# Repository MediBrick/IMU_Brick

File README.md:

# IMU / Activity Brick

This repository contains two generations of the MediBrick IMU board design.

## [v1 — IMU MediBrick](v1/README.md)

The original board, built around the TDK ICM-20948 9-axis IMU and Bosch
BMP581 pressure sensor with an SPI interface. This design is complete and has
been manufactured. ICM-20948 is no longer manufactured.

## [v2 — Activity Brick V2](v2/README.md)

A redesign around the Bosch BMI323 IMU, BMM350 magnetometer, BMP581
barometer, and an optional MAX-M10S or ZED-F9P GNSS/RTK receiver, interfacing
to an Adafruit Feather ESP32-S3 host.

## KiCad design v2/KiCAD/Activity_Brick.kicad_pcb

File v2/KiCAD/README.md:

# Activity Brick V2 KiCad libraries

This directory is ready to hold the Activity Brick V2 KiCad project. KiCad
automatically reads the three project library tables when the project is saved
in this directory.

- `ActivityBrickV2.kicad_pro`: KiCad 10 project entry point
- `ActivityBrickV2.kicad_sch`: main schematic
- `ActivityBrickV2.kicad_pcb`: PCB layout
- `symbols/ActivityBrick.kicad_symdir/`: unpacked project-local symbol library;
  store each symbol in its own `.kicad_sym` file
- `footprints/ActivityBrick.pretty/`: project-local footprint library; store each
  footprint in its own `.kicad_mod` file
- `3dmodels/ActivityBrick.3dshapes/`: project-local STEP and WRL models
- `design_blocks/ActivityBrick.kicad_blocks/`: reusable schematic and PCB blocks

The design-block library contains empty, valid schematic blocks for `Power`,
`Sensors`, `GNSS_MAX_M10S`, `GNSS_ZED_F9P`, and `Feather_Interface`.

The PCB intentionally has no board outline yet. DRC will report
`invalid_outline` until the mechanical board dimensions are defined on
`Edge.Cuts`.

## Creating a design block

1. Open the Activity Brick V2 project in KiCad 10.
2. In the Schematic or PCB Editor, select **View -> Panels -> Design Blocks**.
3. Select the `ActivityBrick` library.
4. Use **Save Selection as Design Block** or **Save Current Sheet as Design Block**.

Keep downloaded or generated symbols and footprints in these project-local
libraries so the design does not depend on a machine-specific global library.
Reference project-local models from footprints using paths such as
`${KIPRJMOD}/3dmodels/ActivityBrick.3dshapes/BMI323.step`.

## Manufacturer component pages

- [Bosch Sensortec BMI323](https://www.bosch-sensortec.com/en/products/motion-sensors/imus/bmi323)
- [Bosch Sensortec BMM350](https://www.bosch-sensortec.com/en/products/motion-sensors/magnetometers/bmm350)
- [Bosch Sensortec BMP581](https://www.bosch-sensortec.com/en/products/environmental-sensors/pressure-sensors/bmp581)
- [u-blox MAX-M10 series (MAX-M10S-00B)](https://www.u-blox.com/en/product/max-m10-series?legacy=Current)
- [u-blox ZED-F9P series (ZED-F9P-05B)](https://www.u-blox.com/en/product/zed-f9p-module)

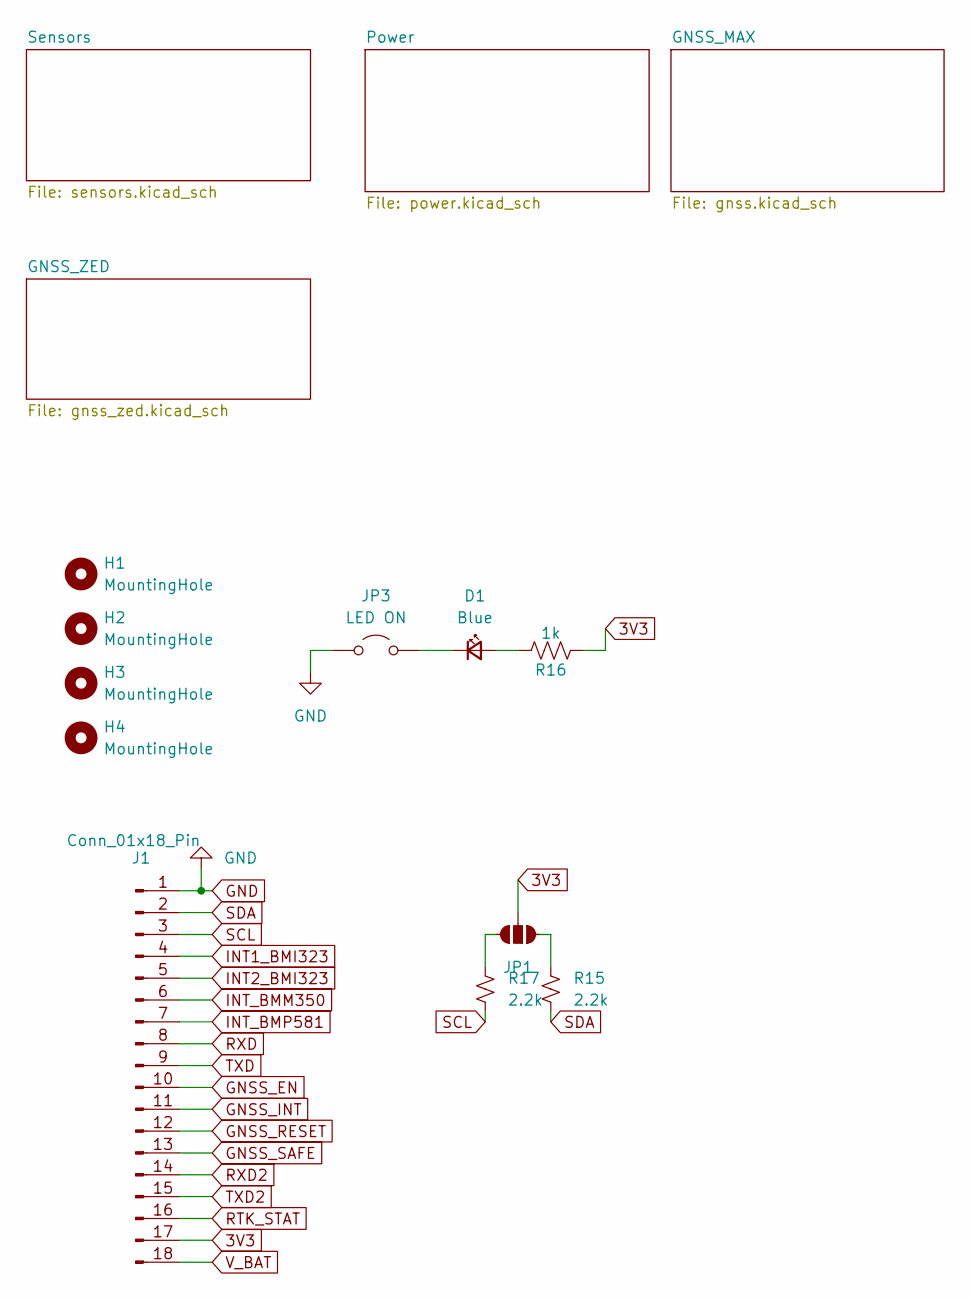
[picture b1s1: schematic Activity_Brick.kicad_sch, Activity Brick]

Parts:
D1: Blue; LED_0402_1005Metric_Red
H1, H2, H3, H4: MountingHole; MountingHole_3.5mm
J1: Conn_01x18_Pin; PinHeader_1x18_P2.54mm_Vertical
JP1: Jumper_3_NO
JP3: LED ON; Jumper_2_NO_NoSilk
R15, R17: 2.2k; R_0402_1005Metric
R16: 1k; R_0402_1005Metric

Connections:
3V3: J1.17, JP1.2 (B), R16.2; also elsewhere on the board
GND: J1.1, JP3.1 (A); also elsewhere on the board
GNSS_EN: J1.10; also elsewhere on the board
GNSS_INT: J1.11; also elsewhere on the board
GNSS_RESET: J1.12; also elsewhere on the board
GNSS_SAFE: J1.13; also elsewhere on the board
INT1_BMI323: J1.4; also elsewhere on the board
INT2_BMI323: J1.5; also elsewhere on the board
INT_BMM350: J1.6; also elsewhere on the board
INT_BMP581: J1.7; also elsewhere on the board
unnamed: D1.2 (A), R16.1
unnamed: D1.1 (K), JP3.2 (B)
unnamed: JP1.1 (A), R15.1
unnamed: JP1.3 (C), R17.1
RTK_STAT: J1.16; also elsewhere on the board
RXD: J1.8; also elsewhere on the board
RXD2: J1.14; also elsewhere on the board
SCL: J1.3, R17.2; also elsewhere on the board
SDA: J1.2, R15.2; also elsewhere on the board
TXD: J1.9; also elsewhere on the board
TXD2: J1.15; also elsewhere on the board
V_BAT: J1.18; also elsewhere on the board

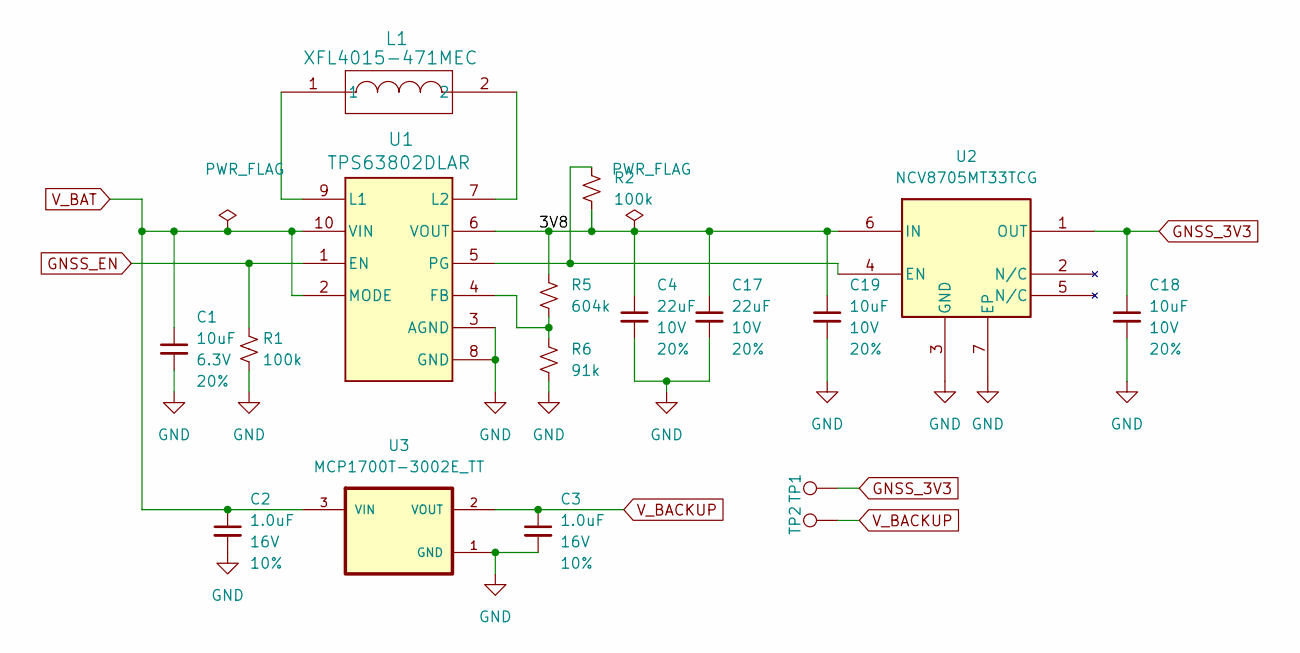
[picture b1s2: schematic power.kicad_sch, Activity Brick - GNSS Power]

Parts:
C1: 10uF; C_0603_1608Metric; Voltage 6.3V; Tolerance 20%
C2, C3: 1.0uF; C_0402_1005Metric; Voltage 16V; Tolerance 10%
C4, C17: 22uF; C_0603_1608Metric; Voltage 10V; Tolerance 20%
C18, C19: 10uF; C_0603_1608Metric; Voltage 10V; Tolerance 20%
L1: XFL4015-471MEC; IND_XFL4015_COC
R1, R2: 100k; R_0402_1005Metric
R5: 604k; R_0402_1005Metric
R6: 91k; R_0402_1005Metric
TP1, TP2: 1.0mm; TestPoint-1.0mm
U1: TPS63802DLAR; DLA0010A
U2: NCV8705MT33TCG; WDFN6_2X2_ONS_NCV8705
U3: MCP1700T-3002E_TT; SOT95P237X112-3N_MCP1700

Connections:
/Power/3V8: C4.1, C17.1, C19.1, R2.2, R5.2, U1.6 (VOUT), U2.6 (IN)
GND: C1.2, C2.2, C3.2, C4.2, C17.2, C18.2, C19.2, R1.2, R6.1, U1.3 (AGND), U1.8 (GND), U2.3 (GND), U2.7 (EP), U3.1 (GND); also elsewhere on the board
GNSS_3V3: C18.1, TP1.1 (1_1), U2.1 (OUT); also elsewhere on the board
GNSS_EN: R1.1, U1.1 (EN); also elsewhere on the board
unnamed: R5.1, R6.2, U1.4 (FB)
unnamed: L1.1, U1.9 (L1)
unnamed: L1.2, U1.7 (L2)
unnamed: R2.1, U1.5 (PG), U2.4 (EN)
V_BACKUP: C3.1, TP2.1 (1_1), U3.2 (VOUT); also elsewhere on the board
V_BAT: C1.1, C2.1, U1.2 (MODE), U1.10 (VIN), U3.3 (VIN); also elsewhere on the board

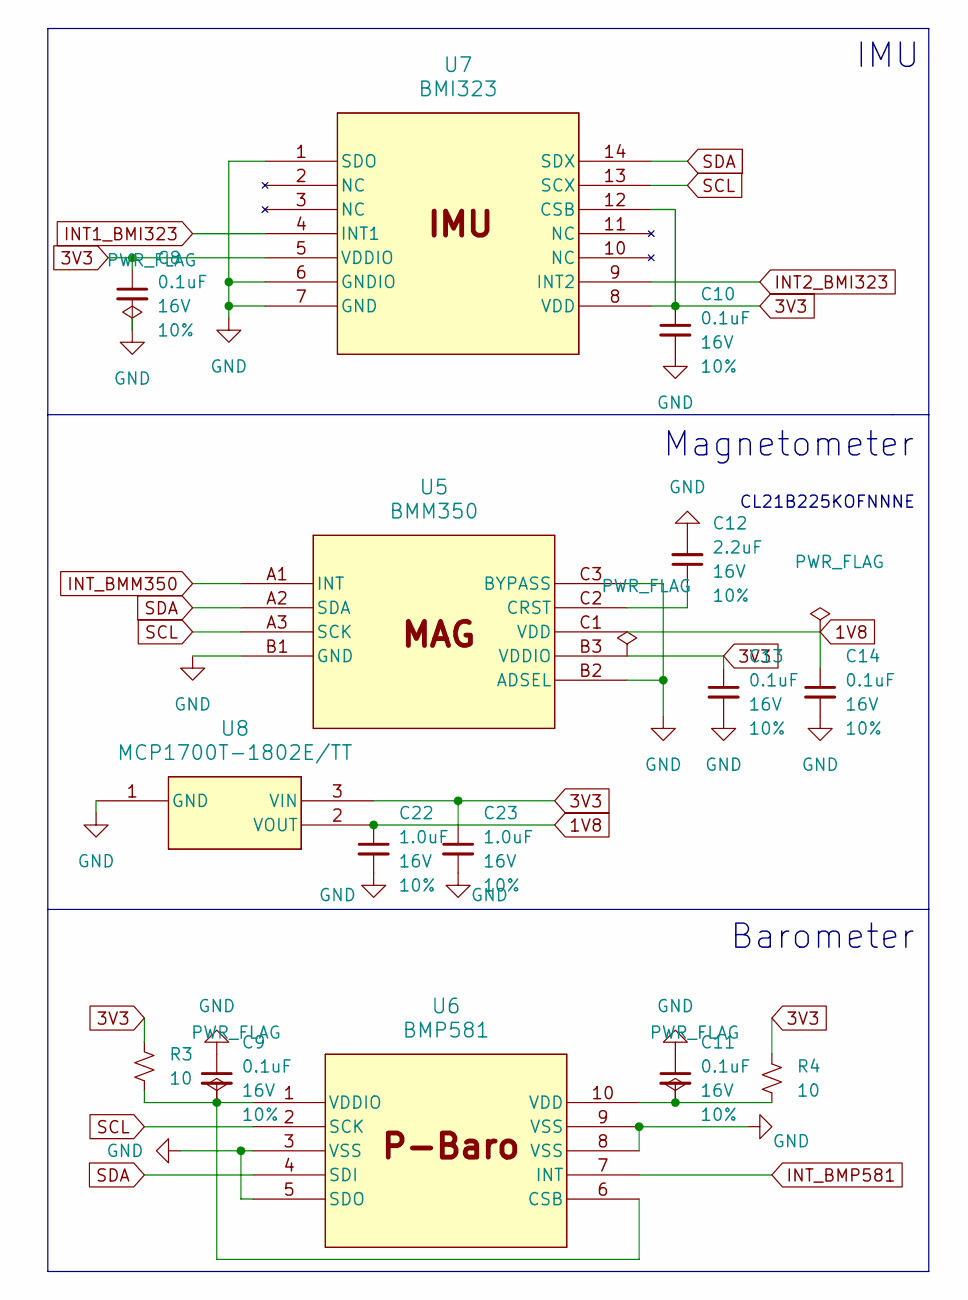
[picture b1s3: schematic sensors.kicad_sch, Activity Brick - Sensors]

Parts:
C8, C9, C10, C11, C13, C14: 0.1uF; C_0402_1005Metric; Voltage 16V; Tolerance 10%
C12: 2.2uF; C_0805_2012Metric; Voltage 16V; Tolerance 10%; MPN CL21B225KOFNNNE
C22, C23: 1.0uF; C_0402_1005Metric; Voltage 16V; Tolerance 10%
R3, R4: 10; R_0402_1005Metric
U5: BMM350; BGA9_BMM350_BOS
U6: BMP581; QFN10_BMP581_BOS
U7: BMI323; BMI323_BOS
U8: MCP1700T-1802E/TT; SOT95P237X112-3N_MCP1700_1802

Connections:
1V8: C14.1, C22.1, U5.C1 (VDD), U8.2 (VOUT)
3V3: C8.1, C10.1, C13.1, C23.1, R3.2, R4.2, U5.B3 (VDDIO), U7.5 (VDDIO), U7.8 (VDD), U7.12 (CSB), U8.3 (VIN); also elsewhere on the board
GND: C8.2, C9.1, C10.2, C11.1, C12.2, C13.2, C14.2, C22.2, C23.2, U5.B1 (GND), U5.B2 (ADSEL), U5.C3 (BYPASS), U6.3 (VSS), U6.5 (SDO), U6.8 (VSS), U6.9 (VSS), U7.1 (SDO), U7.6 (GNDIO), U7.7 (GND), U8.1 (GND); also elsewhere on the board
INT1_BMI323: U7.4 (INT1); also elsewhere on the board
INT2_BMI323: U7.9 (INT2); also elsewhere on the board
INT_BMM350: U5.A1 (INT); also elsewhere on the board
INT_BMP581: U6.7 (INT); also elsewhere on the board
unnamed: C12.1, U5.C2 (CRST)
unnamed: C9.2, R3.1, U6.1 (VDDIO), U6.6 (CSB)
unnamed: C11.2, R4.1, U6.10 (VDD)
SCL: U5.A3 (SCK), U6.2 (SCK), U7.13 (SCX); also elsewhere on the board
SDA: U5.A2 (SDA), U6.4 (SDI), U7.14 (SDX); also elsewhere on the board

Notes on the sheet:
Magnetometer
CL21B225KOFNNNE
IMU
Barometer

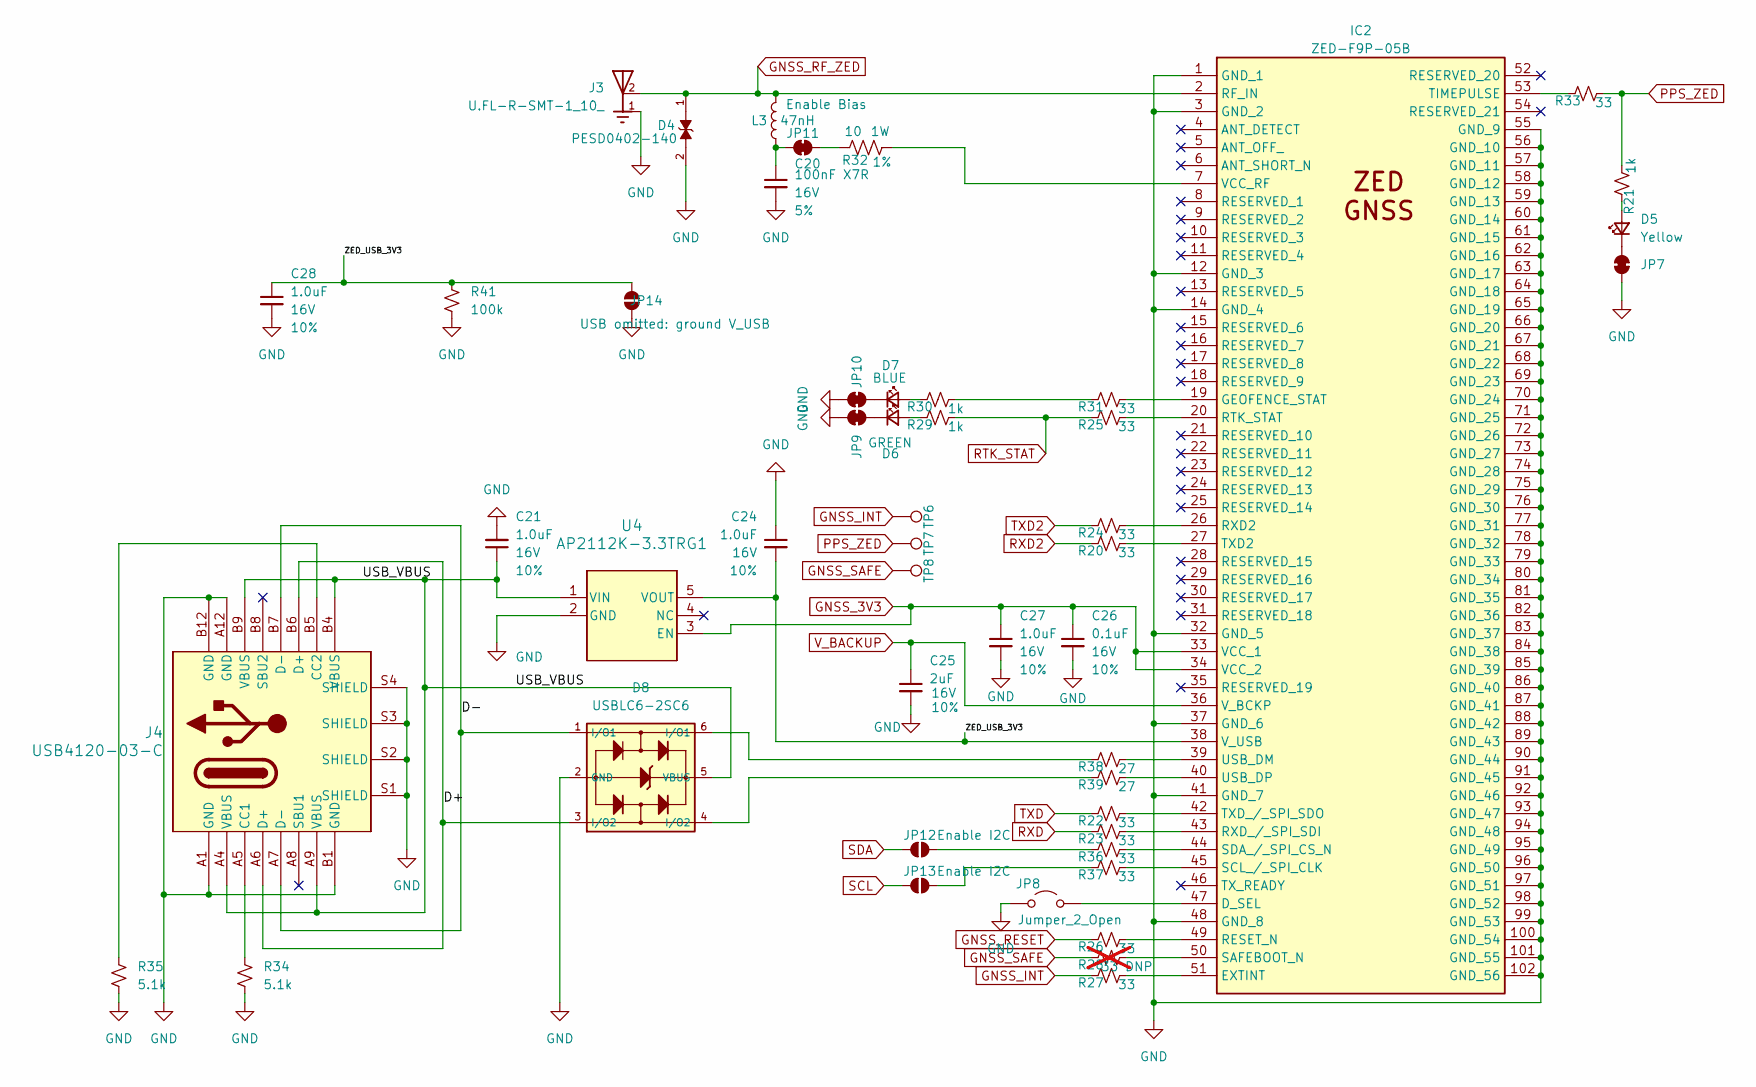
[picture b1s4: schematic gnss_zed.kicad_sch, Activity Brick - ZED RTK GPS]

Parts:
C20: 100nF X7R; C_0402_1005Metric; Voltage 16V; Tolerance 5%; Part Murata GRM155R71C104JA88D
C21, C24, C27, C28: 1.0uF; C_0402_1005Metric; Voltage 16V; Tolerance 10%
C25: 2uF; C_0402_1005Metric; Voltage 16V; Tolerance 10%
C26: 0.1uF; C_0402_1005Metric; Voltage 16V; Tolerance 10%
D4: PESD0402-140; DIO_PESD0402-140; PARTREV 2016
D5: Yellow; LED_0402_1005Metric_Red
D6: GREEN; LED_0402_1005Metric_Red
D7: BLUE; LED_0402_1005Metric_Red
D8: USBLC6-2SC6; USBLC6-2SC6_SOT23-6L
IC2: ZED-F9P-05B; ZEDF9P05B; Manufacturer_Part_Number ZED-F9P-05B; Mouser Part Number 134-ZED-F9P-05B
J3: U.FL-R-SMT-1_10_; HRS_U.FL-R-SMT-1_10_
J4: USB4120-03-C; USB4120-03-C_GCT
JP7, JP9, JP10: Jumper_2_NC_Trace
JP8: Jumper_2_Open; Jumper_2_NO
JP11: Enable Bias; Jumper_2_NC_Trace
JP12, JP13: Enable I2C; Jumper_2_NO
JP14: USB omitted: ground V_USB; Jumper_2_NO
L3: 47nH; L_0402_1005Metric; Part Murata LQG15HS47NJ02D
R20, R22, R23, R24, R25, R26, R27, R31, R33, R36, R37: 33; R_0402_1005Metric
R21, R29, R30: 1k; R_0402_1005Metric
R28: 33 DNP; R_0402_1005Metric; not fitted
R32: 10; R_2010_5025Metric; Tolerance 1%; Part Bourns CMP2010-FX-10R0ELF
R34, R35: 5.1k; R_0402_1005Metric
R38, R39: 27; R_0402_1005Metric
R41: 100k; R_0402_1005Metric
TP6, TP7, TP8: 1.0mm; TestPoint-1.0mm
U4: AP2112K-3.3TRG1; SOT_RG1_DIO_AP2112K

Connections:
/GNSS_ZED/D+: D8.3 (I/O2), J4.A6 (D+), J4.B6 (D+)
/GNSS_ZED/D-: D8.1 (I/O1), J4.A7 (D-), J4.B7 (D-)
/GNSS_ZED/USB_VBUS: C21.1, D8.5 (VBUS), J4.A4 (VBUS), J4.A9 (VBUS), J4.B4 (VBUS), J4.B9 (VBUS), U4.1 (VIN)
/GNSS_ZED/ZED_USB_3V3: C24.2, C28.1, IC2.38 (V_USB), JP14.2 (B), R41.2, U4.5 (VOUT)
GND: C20.2, C21.2, C24.1, C25.2, C26.2, C27.2, C28.2, D4.2, D8.2 (GND), IC2.1 (GND_1), IC2.3 (GND_2), IC2.12 (GND_3), IC2.14 (GND_4), IC2.32 (GND_5), IC2.37 (GND_6), IC2.41 (GND_7), IC2.48 (GND_8), IC2.55 (GND_9), IC2.56 (GND_10), IC2.57 (GND_11), IC2.58 (GND_12), IC2.59 (GND_13), IC2.60 (GND_14), IC2.61 (GND_15), IC2.62 (GND_16), IC2.63 (GND_17), IC2.64 (GND_18), IC2.65 (GND_19), IC2.66 (GND_20), IC2.67 (GND_21), IC2.68 (GND_22), IC2.69 (GND_23), IC2.70 (GND_24), IC2.71 (GND_25), IC2.72 (GND_26), IC2.73 (GND_27), IC2.74 (GND_28), IC2.75 (GND_29), IC2.76 (GND_30), IC2.77 (GND_31), IC2.78 (GND_32), IC2.79 (GND_33), IC2.80 (GND_34), IC2.81 (GND_35), IC2.82 (GND_36), IC2.83 (GND_37), IC2.84 (GND_38), IC2.85 (GND_39), IC2.86 (GND_40), IC2.87 (GND_41), IC2.88 (GND_42), IC2.89 (GND_43), IC2.90 (GND_44), IC2.91 (GND_45), IC2.92 (GND_46), IC2.93 (GND_47), IC2.94 (GND_48), IC2.95 (GND_49), IC2.96 (GND_50), IC2.97 (GND_51), IC2.98 (GND_52), IC2.99 (GND_53), IC2.100 (GND_54), IC2.101 (GND_55), IC2.102 (GND_56), J3.1, J3.3, J4.A1 (GND), J4.A12 (GND), J4.B1 (GND), J4.B12 (GND), J4.S1 (SHIELD), J4.S2 (SHIELD), J4.S3 (SHIELD), J4.S4 (SHIELD), JP7.1 (A), JP8.1 (A), JP9.1 (A), JP10.1 (A), JP14.1 (A), R34.1, R35.1, R41.1, U4.2 (GND); also elsewhere on the board
GNSS_3V3: C26.1, C27.1, IC2.33 (VCC_1), IC2.34 (VCC_2), U4.3 (EN); also elsewhere on the board
GNSS_INT: R27.1, TP6.1 (1_1); also elsewhere on the board
GNSS_RESET: R26.1; also elsewhere on the board
GNSS_RF_ZED: D4.1, IC2.2 (RF_IN), J3.2, L3.2
GNSS_SAFE: R28.1, TP8.1 (1_1); also elsewhere on the board
unnamed: D5.2 (A), R21.1
unnamed: D5.1 (K), JP7.2 (B)
unnamed: D6.2 (A), R29.1
unnamed: D6.1 (K), JP9.2 (B)
unnamed: D7.2 (A), R30.1
unnamed: D7.1 (K), JP10.2 (B)
unnamed: D8.6 (I/O1), R38.1
unnamed: D8.4 (I/O2), R39.1
unnamed: IC2.47 (D_SEL), JP8.2 (B)
unnamed: IC2.51 (EXTINT), R27.2
unnamed: IC2.19 (GEOFENCE_STAT), R31.2
unnamed: IC2.49 (RESET_N), R26.2
unnamed: IC2.20 (RTK_STAT), R25.2
unnamed: IC2.26 (RXD2), R24.2
unnamed: IC2.43 (RXD_/_SPI_SDI), R23.2
unnamed: IC2.50 (SAFEBOOT_N), R28.2
unnamed: IC2.45 (SCL_/_SPI_CLK), R37.2
unnamed: IC2.44 (SDA_/_SPI_CS_N), R36.2
unnamed: IC2.53 (TIMEPULSE), R33.1
unnamed: IC2.27 (TXD2), R20.2
unnamed: IC2.42 (TXD_/_SPI_SDO), R22.2
unnamed: IC2.39 (USB_DM), R38.2
unnamed: IC2.40 (USB_DP), R39.2
unnamed: IC2.7 (VCC_RF), R32.2
unnamed: J4.A5 (CC1), R34.2
unnamed: J4.B5 (CC2), R35.2
unnamed: C20.1, JP11.1 (A), L3.1
unnamed: JP11.2 (B), R32.1
unnamed: JP12.2 (B), R36.1
unnamed: JP13.2 (B), R37.1
unnamed: R30.2, R31.1
PPS_ZED: R21.2, R33.2, TP7.1 (1_1)
RTK_STAT: R25.1, R29.2; also elsewhere on the board
RXD: R23.1; also elsewhere on the board
RXD2: R20.1; also elsewhere on the board
SCL: JP13.1 (A); also elsewhere on the board
SDA: JP12.1 (A); also elsewhere on the board
TXD: R22.1; also elsewhere on the board
TXD2: R24.1; also elsewhere on the board
V_BACKUP: C25.1, IC2.36 (V_BCKP); also elsewhere on the board

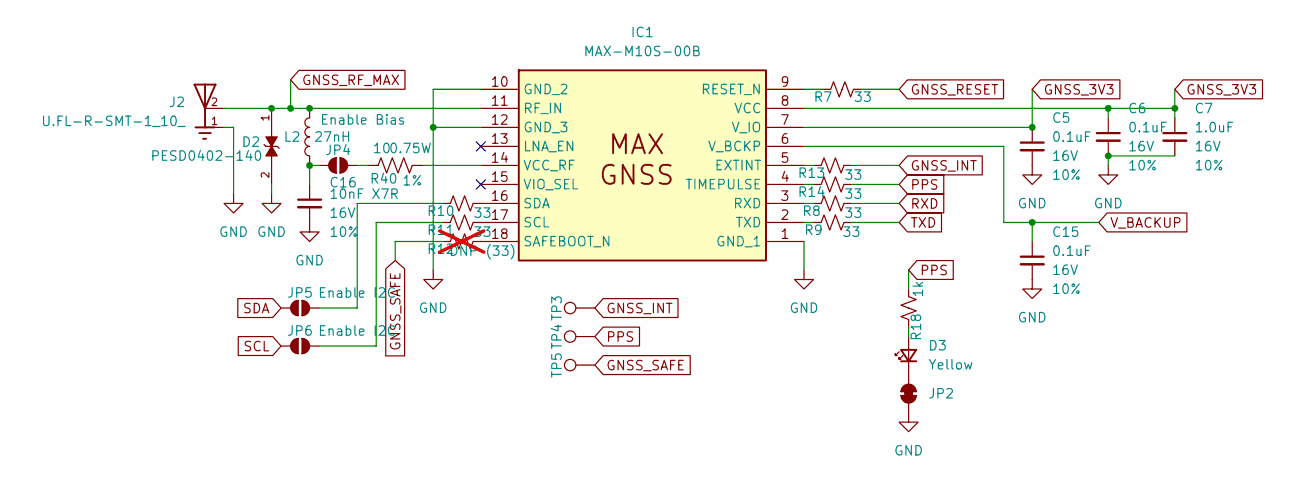
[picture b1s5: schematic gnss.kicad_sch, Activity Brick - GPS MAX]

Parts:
C5, C6, C15: 0.1uF; C_0402_1005Metric; Voltage 16V; Tolerance 10%
C7: 1.0uF; C_0402_1005Metric; Voltage 16V; Tolerance 10%
C16: 10nF X7R; C_0402_1005Metric; Voltage 16V; Tolerance 10%
D2: PESD0402-140; DIO_PESD0402-140; PARTREV 2016
D3: Yellow; LED_0402_1005Metric_Red
IC1: MAX-M10S-00B; MAXM10S00B; Manufacturer_Part_Number MAX-M10S-00B; Mouser Part Number 377-MAX-M10S-00B
J2: U.FL-R-SMT-1_10_; HRS_U.FL-R-SMT-1_10_
JP2: Jumper_2_NC_Trace
JP4: Enable Bias; Jumper_2_NO
JP5, JP6: Enable I2C; Jumper_2_NO
L2: 27nH; L_0402_1005Metric; Part Murata `LQG15HN27NH02D`
R7, R8, R9, R10, R11, R13, R14: 33; R_0402_1005Metric
R12: DNP (33); R_0402_1005Metric; not fitted
R18: 1k; R_0402_1005Metric
R40: 10; R_1210_3225Metric; Tolerance 1%; Part VISHAY CRCW121010R0FKEAHP 0.75W 1210
TP3, TP4, TP5: 1.0mm; TestPoint-1.0mm

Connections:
GND: C5.2, C6.2, C7.2, C15.2, C16.2, D2.2, IC1.1 (GND_1), IC1.10 (GND_2), IC1.12 (GND_3), J2.1, J2.3, JP2.1 (A); also elsewhere on the board
GNSS_3V3: C5.1, C6.1, C7.1, IC1.7 (V_IO), IC1.8 (VCC); also elsewhere on the board
GNSS_INT: R13.2, TP3.1 (1_1); also elsewhere on the board
GNSS_RESET: R7.2; also elsewhere on the board
GNSS_RF_MAX: D2.1, IC1.11 (RF_IN), J2.2, L2.2
GNSS_SAFE: R12.1, TP5.1 (1_1); also elsewhere on the board
unnamed: D3.2 (A), R18.1
unnamed: D3.1 (K), JP2.2 (B)
unnamed: IC1.5 (EXTINT), R13.1
unnamed: IC1.9 (RESET_N), R7.1
unnamed: IC1.3 (RXD), R8.1
unnamed: IC1.18 (SAFEBOOT_N), R12.2
unnamed: IC1.17 (SCL), R11.2
unnamed: IC1.16 (SDA), R10.2
unnamed: IC1.4 (TIMEPULSE), R14.1
unnamed: IC1.2 (TXD), R9.1
unnamed: IC1.14 (VCC_RF), R40.2
unnamed: C16.1, JP4.1 (A), L2.1
unnamed: JP4.2 (B), R40.1
unnamed: JP5.2 (B), R10.1
unnamed: JP6.2 (B), R11.1
PPS: R14.2, R18.2, TP4.1 (1_1)
RXD: R8.2; also elsewhere on the board
SCL: JP6.1 (A); also elsewhere on the board
SDA: JP5.1 (A); also elsewhere on the board
TXD: R9.2; also elsewhere on the board
V_BACKUP: C15.1, IC1.6 (V_BCKP); also elsewhere on the board

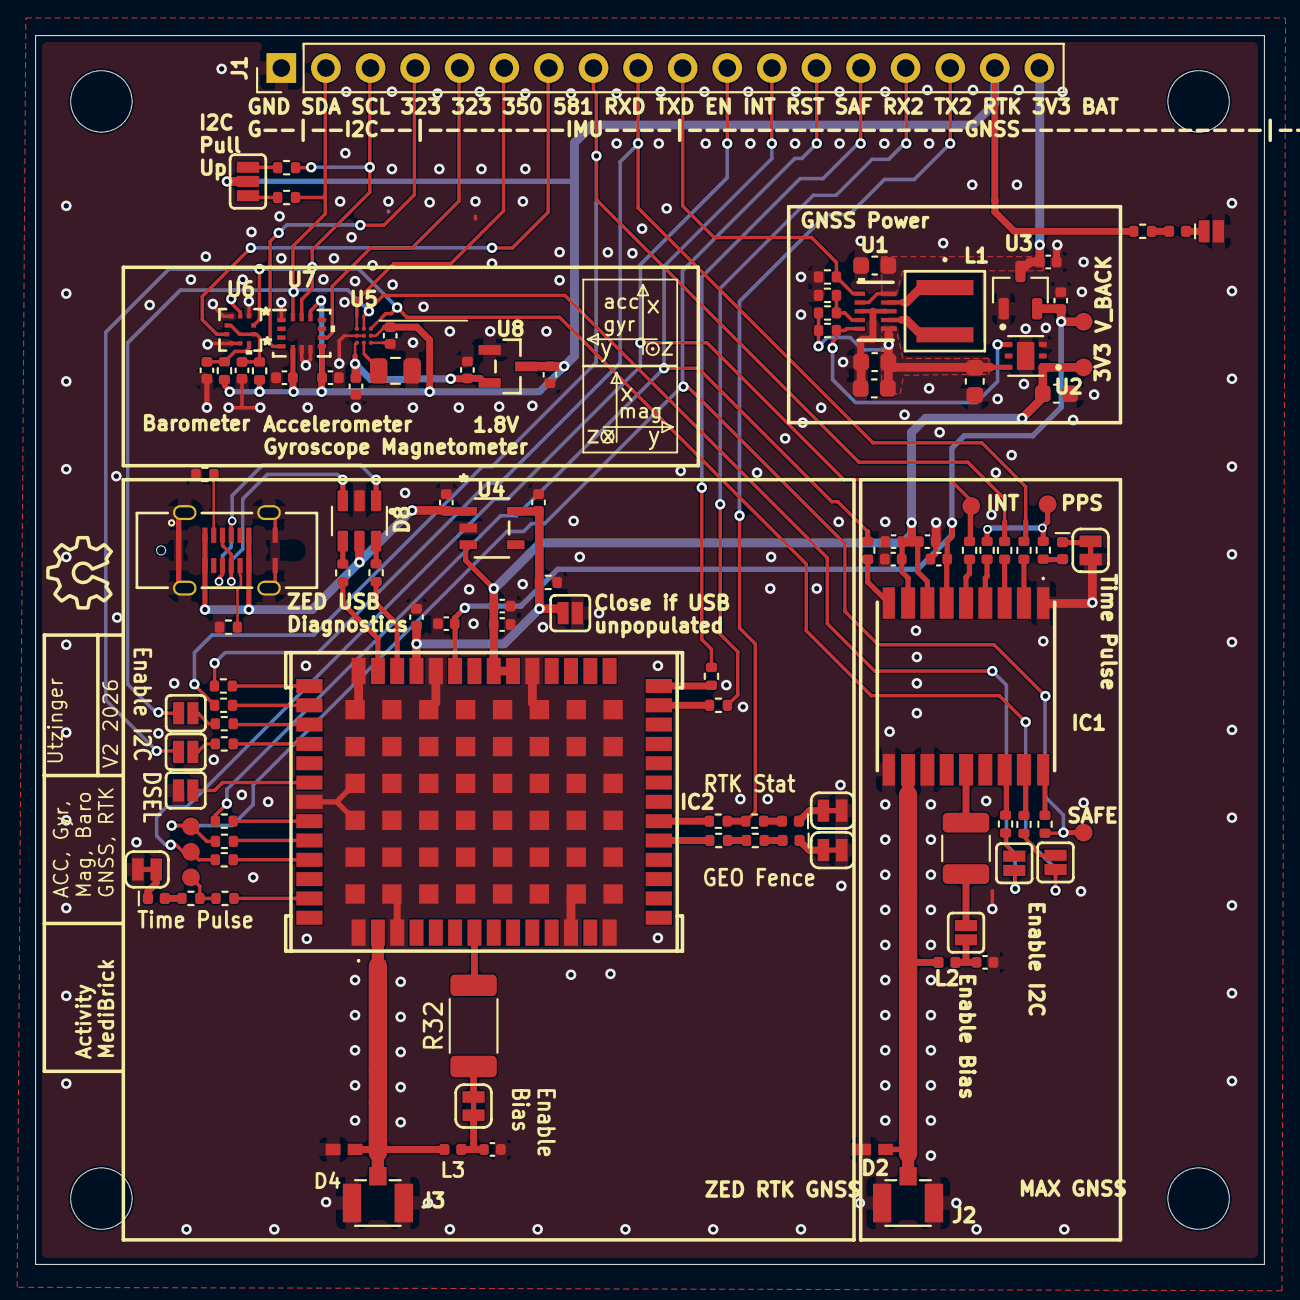
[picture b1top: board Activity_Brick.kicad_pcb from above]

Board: 2 copper layers, 70.0 x 70.0 mm, 120 parts (0 on the bottom side), 87 nets.

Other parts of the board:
G1: OSHW_Logo; Creative_Commons_License

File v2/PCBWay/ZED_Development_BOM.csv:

Line #,Quantity,Designator,MFG Part Number,Footprint,Manufacturer,Description,Type (SMD/THT),Distributor,Distributor Part Number,Value,
1,1,C1,GRM188R60J106ME47D,C_0603_1608Metric,Murata,"Unpolarized capacitor, X5R/X7R",SMD,LCSC,C77041,10uF,
2,4,"C2, C3, C22, C23",GRM155R61C105KE01D,C_0402_1005Metric,Murata,Unpolarized capacitor,SMD,LCSC,C77007,1.0uF,
3,1,C4,GRM188R61A226ME15D,C_0603_1608Metric,Murata,"Unpolarized capacitor, X5R",SMD,LCSC,C84419,22uF,
4,6,"C8, C9, C10, C11, C13, C14",GRM155R71C104KA88D,C_0402_1005Metric,Murata,Unpolarized capacitor,SMD,LCSC,C71629,0.1uF,
5,1,C12,CL21B225KOFNNNE,C_0805_2012Metric,Samsung,"BMM350 CRST capacitor, 2.2 uF, low ESR/ESL, nonmagnetic required",SMD,LCSC,C28234,2.2uF,
6,1,C17,GRM188R61A226ME15D,C_0603_1608Metric,Murata,"Unpolarized capacitor, X5R/X7R",SMD,LCSC,C84419,22uF,
7,2,"C18, C19",GRM188R61A106ME69D,C_0603_1608Metric,Murata,"Unpolarized capacitor, X5R",SMD,LCSC,C90053,10uF,
8,1,D1,XL-1005UBC,LED_0402_1005Metric_Blue,XINGLIGHT,Light emitting diode,SMD,LCSC,C22355736,Blue,
9,1,L1,XFL4015-471MEC,IND_XFL4015_COC,Coilcraft,Inductor,SMD,LCSC,C18221164,XFL4015-471MEC,
10,2,"R1, R2",RC0402FR-07100KL,R_0402_1005Metric,Yageo,Resistor,SMD,LCSC,C60491,100k,
11,2,"R3, R4",RC0402FR-0710RL,R_0402_1005Metric,Yageo,Resistor,SMD,LCSC,C138066,10,
12,1,R5,CRCW0402604KFKED,R_0402_1005Metric,Vishay,Resistor,SMD,LCSC,C2085221,604k,
13,1,R6,AC0402FR-0791KL,R_0402_1005Metric,Yageo,Resistor,SMD,LCSC,C144733,91k,
14,2,"R15, R17",RC0402FR-072K2L,R_0402_1005Metric,Yageo,Resistor,SMD,LCSC,C114762,2.2k,
15,1,R16,RC0402FR-071KL,R_0402_1005Metric,Yageo,Resistor,SMD,LCSC,C106235,1k,
16,1,U1,TPS63802DLAR,DLA0010A,Texas Instruments,Buck-Boost,SMD,LCSC,C2845237,TPS63802DLAR,
17,1,U2,NCV8705MT33TCG,WDFN6_2X2_ONS_NCV8705,onsemi,"500 mA ultra-low-noise 3.3 V LDO, WDFN6, onsemi",SMD,LCSC,C604084,NCV8705MT33TCG,
18,1,U3,MCP1700T-3002E/TT,SOT95P237X112-3N_MCP1700,Microchip Technology,"MCP1700T-3002E/TT,LDOVoltage Regulator,250mA,3V +/-2%,2.3 to 6Vin,3-Pin SOT-23 | Microchip Technology Inc. MCP1700T-3002E/TT",SMD,LCSC,C62244,MCP1700T-3002E_TT,
19,1,U5,BMM350,BGA9_BMM350_BOS,Bosch Sensortec,Magnetomoer,SMD,LCSC,C17225907,BMM350,
20,1,U6,BMP581,QFN10_BMP581_BOS,Bosch Sensortec,Barometer,SMD,LCSC,C5362283,BMP581,
21,1,U7,BMI323,BMI323_BOS,Bosch Sensortec,IMU,SMD,LCSC,C5368700,BMI323,
22,1,U8,MCP1700T-1802E/TT,SOT95P237X112-3N_MCP1700_1802,Microchip Technology,LDO Regulator,SMD,LCSC,C150796,MCP1700T-1802E/TT,
23,2,"C21, C24",GRM155R61C105KE01D,C_0402_1005Metric,Murata,Unpolarized capacitor,SMD,LCSC,C77007,1.0uF,
24,1,C28,GRM155R61C105KE01D,C_0402_1005Metric,Murata,Unpolarized capacitor,SMD,LCSC,C77007,1.0uF,
25,1,D8,USBLC6-2SC6,USBLC6-2SC6_SOT23-6L,STMicroelectronics,17V Clamp 5A (8/20µs) Ipp Tvs Diode,SMD,LCSC,C7519,USBLC6-2SC6,
26,1,J4,USB4120-03-C,USB4120-03-C_GCT,GCT,USB C receptacle,Hybrid,LCSC,C3445864,USB4120-03-C,
27,2,"R34, R35",RC0402FR-075K1L,R_0402_1005Metric,Yageo,Resistor,SMD,LCSC,C105872,5.1k,
28,2,"R38, R39",RC0402FR-0727RL,R_0402_1005Metric,Yageo,Resistor,SMD,LCSC,C138021,27,
29,1,R41,RC0402FR-07100KL,R_0402_1005Metric,Yageo,Resistor,SMD,LCSC,C60491,100k,
30,1,U4,AP2112K-3.3TRG1,SOT_RG1_DIO_AP2112K,Diodes Incorporated,LDO Regulator,SMD,LCSC,C51118,AP2112K-3.3TRG1,
31,1,C20,GRM155R71C104JA88D,C_0402_1005Metric,Murata,"Murata GRM155R71C104JA88D, 100 nF, 5%, 16 V, X7R, 0402",SMD,LCSC,C913742,100nF,
32,1,C25,GRM155R61C225KE44D,C_0402_1005Metric,Murata,Unpolarized capacitor,SMD,LCSC,C335109,2.2uF,
33,1,C26,GRM155R71C104KA88D,C_0402_1005Metric,Murata,Unpolarized capacitor,SMD,LCSC,C71629,0.1uF,
34,1,C27,GRM155R61C105KE01D,C_0402_1005Metric,Murata,Unpolarized capacitor,SMD,LCSC,C77007,1.0uF,
35,1,D4,PESD0402-140,DIO_PESD0402-140,Littelfuse,40V Clamp - Ipp Tvs Diode,SMD,LCSC,C10662,PESD0402-140,
36,1,D5,XL-1005UYC,LED_0402_1005Metric_Red,XINGLIGHT,Light emitting diode,SMD,LCSC,C25503856,Yellow,
37,1,D6,XL-1005UGC,LED_0402_1005Metric_Red,XINGLIGHT,Light emitting diode,SMD,LCSC,C965793,GREEN,
38,1,D7,XL-1005UBC,LED_0402_1005Metric_Red,XINGLIGHT,Light emitting diode,SMD,LCSC,C22355736,BLUE,
39,1,IC2,ZED-F9P-05B,ZEDF9P05B,u-blox,"GNSS / GPS Modules High Precision Multi-band RTK  GNSS module, with Galileo OSNMA",SMD,Mouser,134-ZED-F9P-05B,ZED-F9P-05B,APPROVED MOUSER SOURCE: 134-ZED-F9P-05B matches exact u-blox ZED-F9P-05B. LCSC C5120257 is -04B and is not approved as a substitute.
40,1,J3,U.FL-R-SMT-1(10),HRS_U.FL-R-SMT-1_10_,Hirose,"U.FL (UMCC) Connector Receptacle, Male Pin 50 Ohms Surface Mount Solder",SMD,LCSC,C88373,U.FL-R-SMT-1_10_,
41,1,L3,LQG15HS47NJ02D,L_0402_1005Metric,Murata,"Inductor, Murata LQG15H, LQW15A Series 47nH 5%",SMD,LCSC,C97998,47nH,
42,11,"R20, R22, R23, R24, R25, R26, R27, R31, R33, R36, R37",RC0402FR-0733RL,R_0402_1005Metric,Yageo,Resistor,SMD,LCSC,C138002,33,
43,3,"R21, R29, R30",RC0402FR-071KL,R_0402_1005Metric,Yageo,Resistor,SMD,LCSC,C106235,1k,
44,1,R32,CMP2010-FX-10R0ELF,R_2010_5025Metric,Bourns,Resistor,SMD,LCSC,C1880468,10,

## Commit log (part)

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2025-12-08 Add initial README for IMU_Brick project
2025-12-08 Release
2025-12-09 Documentation

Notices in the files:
parts and their libraries:
Released under the Creative Commons Attribution Share-Alike 4.0 License
https://creativecommons.org/licenses/by-sa/4.0
